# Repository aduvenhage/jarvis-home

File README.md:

# jarvis-home (not active)
Home automation and DIY security project.
Still used, but not actively developed anymore.

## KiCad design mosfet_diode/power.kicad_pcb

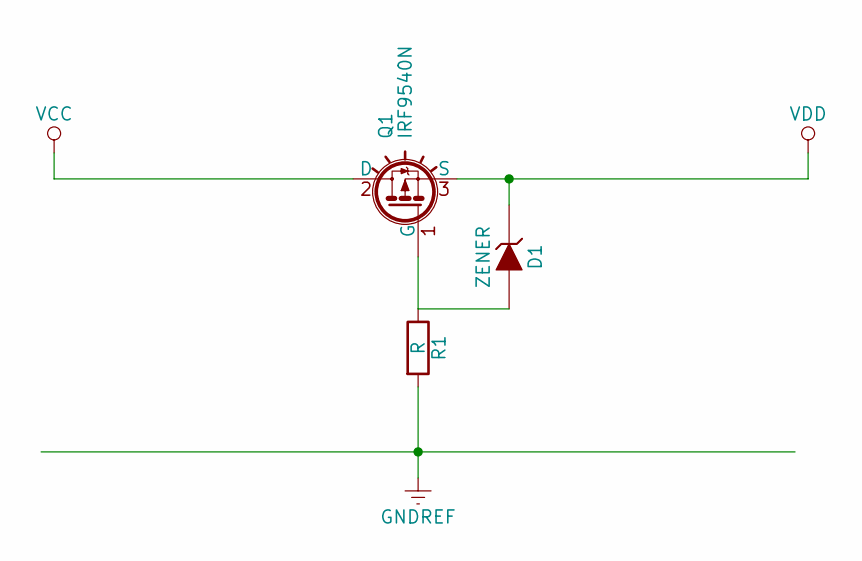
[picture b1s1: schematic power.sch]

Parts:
D1: ZENER; D_DO-35_SOD27_P7.62mm_Horizontal
Q1: IRF9540N; TO-220_Horizontal
R1: R; R_Axial_DIN0207_L6.3mm_D2.5mm_P10.16mm_Horizontal

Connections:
GNDREF: R1.2
unnamed: D1.2 (A), Q1.1 (G), R1.1
VCC: Q1.2 (D)
VDD: D1.1 (K), Q1.3 (S)

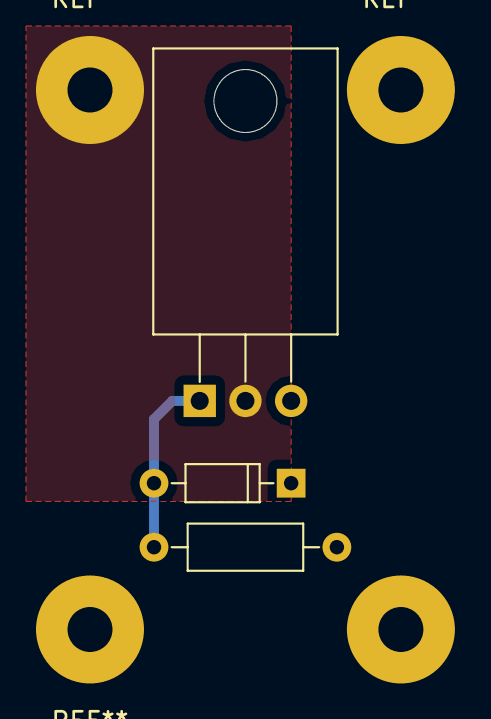
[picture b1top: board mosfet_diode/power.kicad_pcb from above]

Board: 2 copper layers, 3 parts (0 on the bottom side), 2 nets.

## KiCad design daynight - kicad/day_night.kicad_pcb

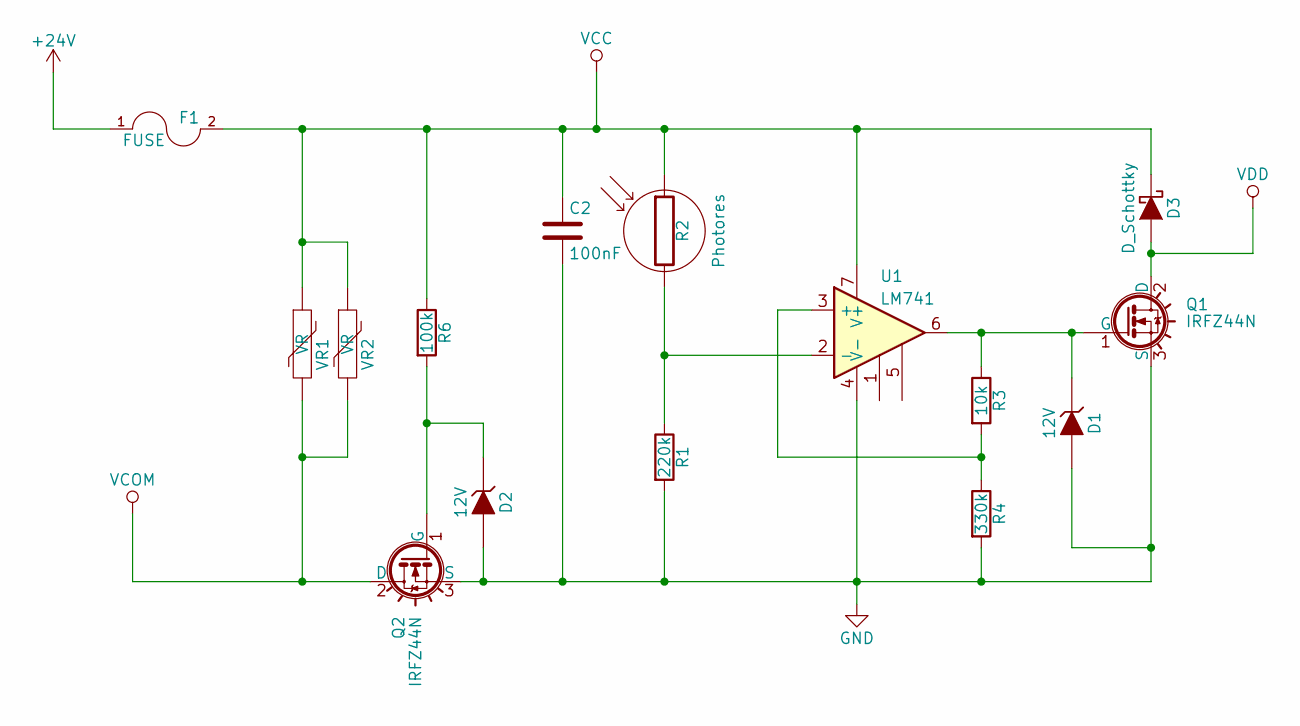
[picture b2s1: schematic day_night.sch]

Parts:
C2: 100nF; C_Disc_D3.4mm_W2.1mm_P2.50mm
D1, D2: 12V; D_DO-35_SOD27_P2.54mm_Vertical_AnodeUp
D3: D_Schottky; D_DO-15_P10.16mm_Horizontal
F1: FUSE; RV_Disc_D21.5_W4.3_P10
Q1, Q2: IRFZ44N; TO-220_Neutral123_Vertical
R1: 220k; R_Axial_DIN0204_L3.6mm_D1.6mm_P2.54mm_Vertical
R2: Photores; R1
R3: 10k; R_Axial_DIN0204_L3.6mm_D1.6mm_P2.54mm_Vertical
R4: 330k; R_Axial_DIN0204_L3.6mm_D1.6mm_P2.54mm_Vertical
R6: 100k; R_Axial_DIN0204_L3.6mm_D1.6mm_P2.54mm_Vertical
U1: LM741; DIP-8_W7.62mm
VR1, VR2: VR; RV_Disc_D9_W3.7_P5

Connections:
+24V: F1.1; also elsewhere on the board
GND: C2.2, D1.2 (A), D2.2 (A), Q1.3 (S), Q2.3 (S), R1.2, R4.2, U1.4 (V-)
unnamed: D1.1 (K), Q1.1 (G), R3.1, U1.6
unnamed: D2.1 (K), Q2.1 (G), R6.2
unnamed: R1.1, R2.2, U1.2 (-)
unnamed: R3.2, R4.1, U1.3 (+)
VCC: C2.1, D3.1 (K), F1.2, R2.1, R6.1, U1.7 (V+), VR1.1, VR2.1; also elsewhere on the board
VCOM: Q2.2 (D), VR1.2, VR2.2; also elsewhere on the board
VDD: D3.2 (A), Q1.2 (D); also elsewhere on the board

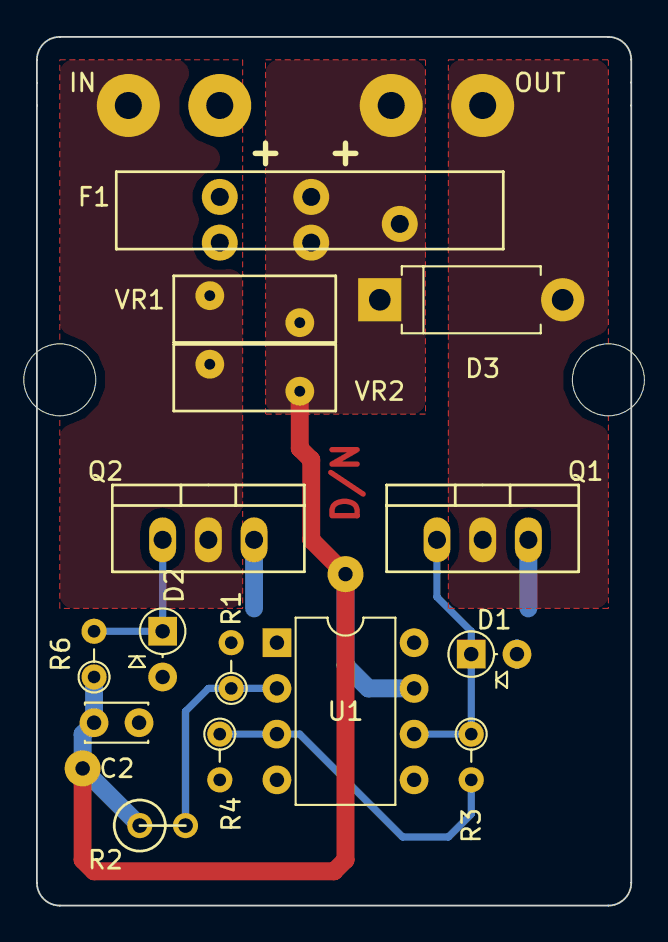
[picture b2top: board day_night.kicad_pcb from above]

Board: 2 copper layers, 33.0 x 48.3 mm, 17 parts (0 on the bottom side), 9 nets.

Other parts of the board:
IN: SolderWirePad_2x_1-5mmDrill
OUT: SolderWirePad_2x_1-5mmDrill

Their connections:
+24V: IN.1; also elsewhere on the board
VCC: OUT.1; also elsewhere on the board
VCOM: IN.1; also elsewhere on the board
VDD: OUT.1; also elsewhere on the board

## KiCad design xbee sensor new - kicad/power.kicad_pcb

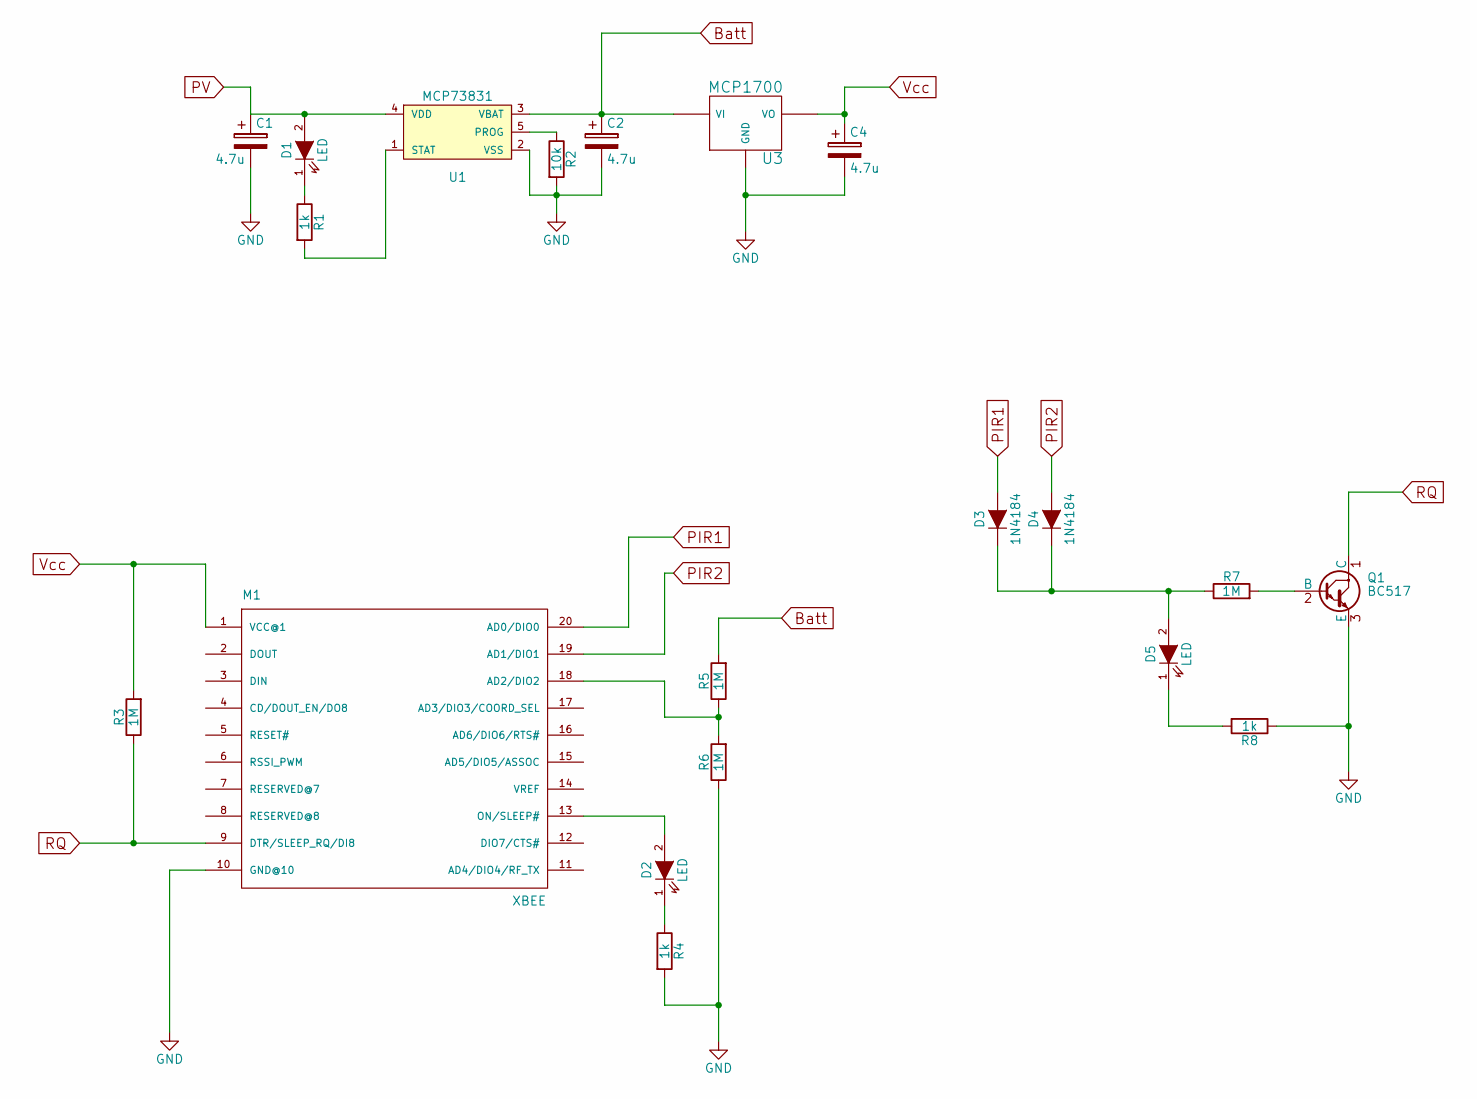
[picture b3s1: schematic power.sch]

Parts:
C1, C2, C4: 4.7u; CP_Radial_D5.0mm_P2.50mm
D1, D2, D5: LED; LED_D3.0mm
D3, D4: 1N4184; D_DO-35_SOD27_P7.62mm_Horizontal
M1: XBEE
Q1: BC517; TO-92_Inline_Narrow_Oval
R1, R4, R8: 1k; R_Axial_DIN0204_L3.6mm_D1.6mm_P7.62mm_Horizontal
R2: 10k; R_Axial_DIN0204_L3.6mm_D1.6mm_P7.62mm_Horizontal
R3, R5, R6, R7: 1M; R_Axial_DIN0204_L3.6mm_D1.6mm_P7.62mm_Horizontal
U1: MCP73831; SOT-23-5_HandSoldering
U3: MCP1700; TO-92_Inline_Narrow_Oval

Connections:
Batt: C2.1, R5.2, U1.3 (VBAT), U3.2 (VI); also elsewhere on the board
GND: C1.2, C2.2, C4.2, M1.10 (GND@10), Q1.3 (E), R2.2, R4.2, R6.1, R8.1, U1.2 (VSS), U3.1 (GND); also elsewhere on the board
unnamed: D1.1 (K), R1.1
unnamed: D2.1 (K), R4.1
unnamed: D2.2 (A), M1.13 (ON/SLEEP#)
unnamed: D3.1 (K), D4.1 (K), D5.2 (A), R7.1
unnamed: D5.1 (K), R8.2
unnamed: M1.18 (AD2/DIO2), R5.1, R6.2
unnamed: Q1.2 (B), R7.2
unnamed: R1.2, U1.1 (STAT)
unnamed: R2.1, U1.5 (PROG)
PIR1: D3.2 (A), M1.20 (AD0/DIO0)
PIR2: D4.2 (A), M1.19 (AD1/DIO1)
PV: C1.1, D1.2 (A), U1.4 (VDD); also elsewhere on the board
RQ: M1.9 (DTR/SLEEP_RQ/DI8), Q1.1 (C), R3.1
Vcc: C4.1, M1.1 (VCC@1), R3.2, U3.3 (VO)

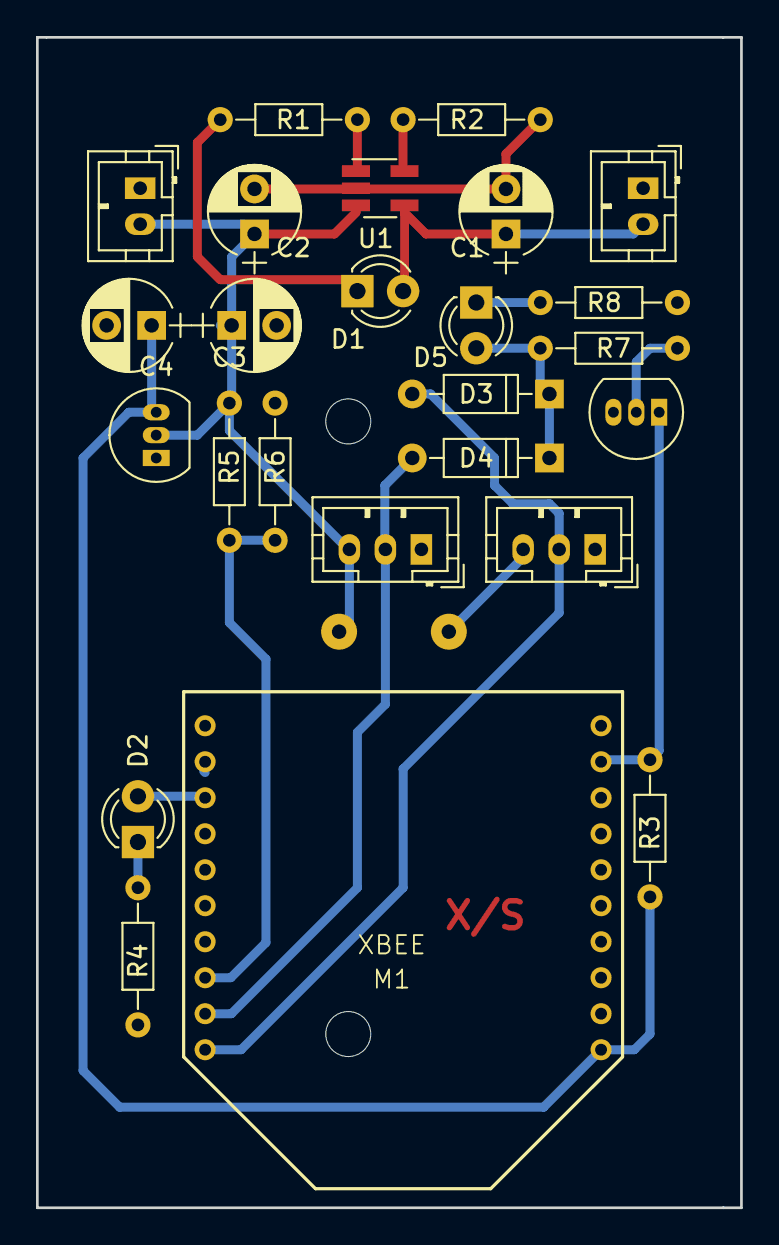
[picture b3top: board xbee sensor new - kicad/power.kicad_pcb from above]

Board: 2 copper layers, 39.1 x 65.0 mm, 23 parts (0 on the bottom side), 16 nets.

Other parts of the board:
Batt: JST_PH_B2B-PH-K_02x2.00mm_Straight
C3: 1u; CP_Radial_D5.0mm_P2.50mm
PV: JST_PH_B2B-PH-K_02x2.00mm_Straight

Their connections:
Batt: Batt.2, C3.1; also elsewhere on the board
GND: Batt.1, C3.2, PV.1; also elsewhere on the board
PV: PV.2; also elsewhere on the board

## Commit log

2017-07-04 first set of files
2017-07-04 added first sensor schematic
2017-07-04 just added new xbee sensor (WIP) schematic
2017-07-04 just added new day-night circuit
2017-07-22 new code uploaded to base station
2017-08-03 created a simple mosfet diode circuit
